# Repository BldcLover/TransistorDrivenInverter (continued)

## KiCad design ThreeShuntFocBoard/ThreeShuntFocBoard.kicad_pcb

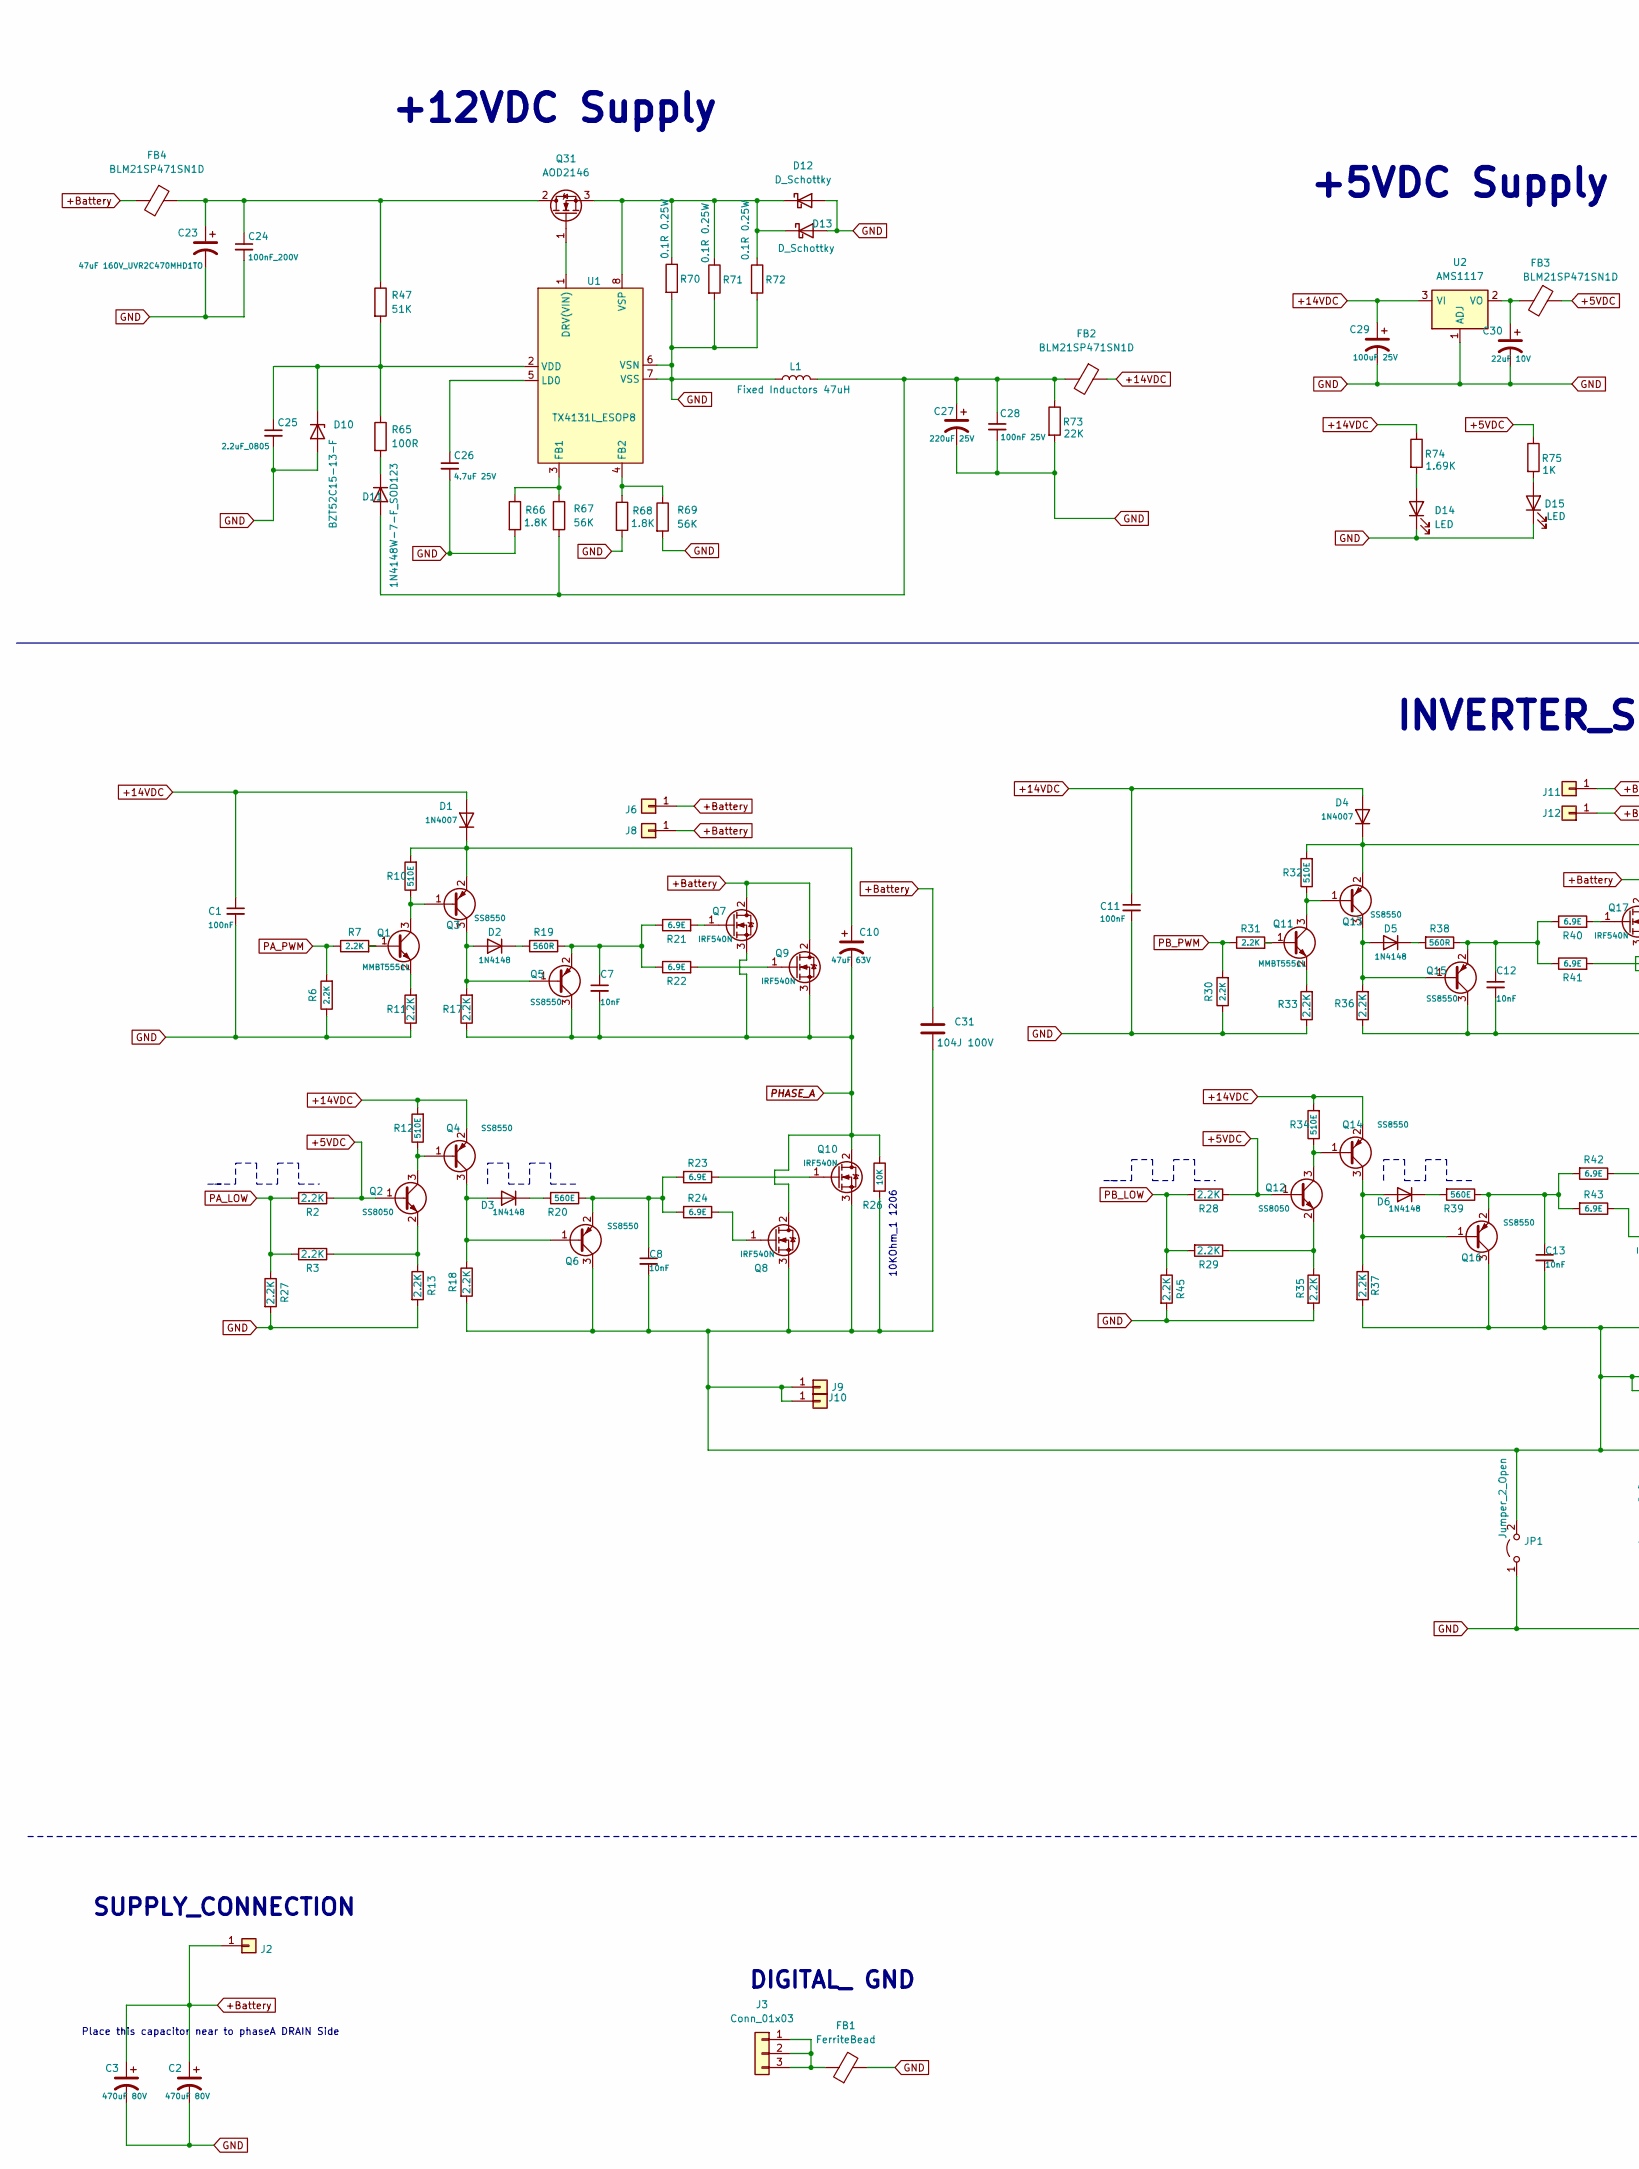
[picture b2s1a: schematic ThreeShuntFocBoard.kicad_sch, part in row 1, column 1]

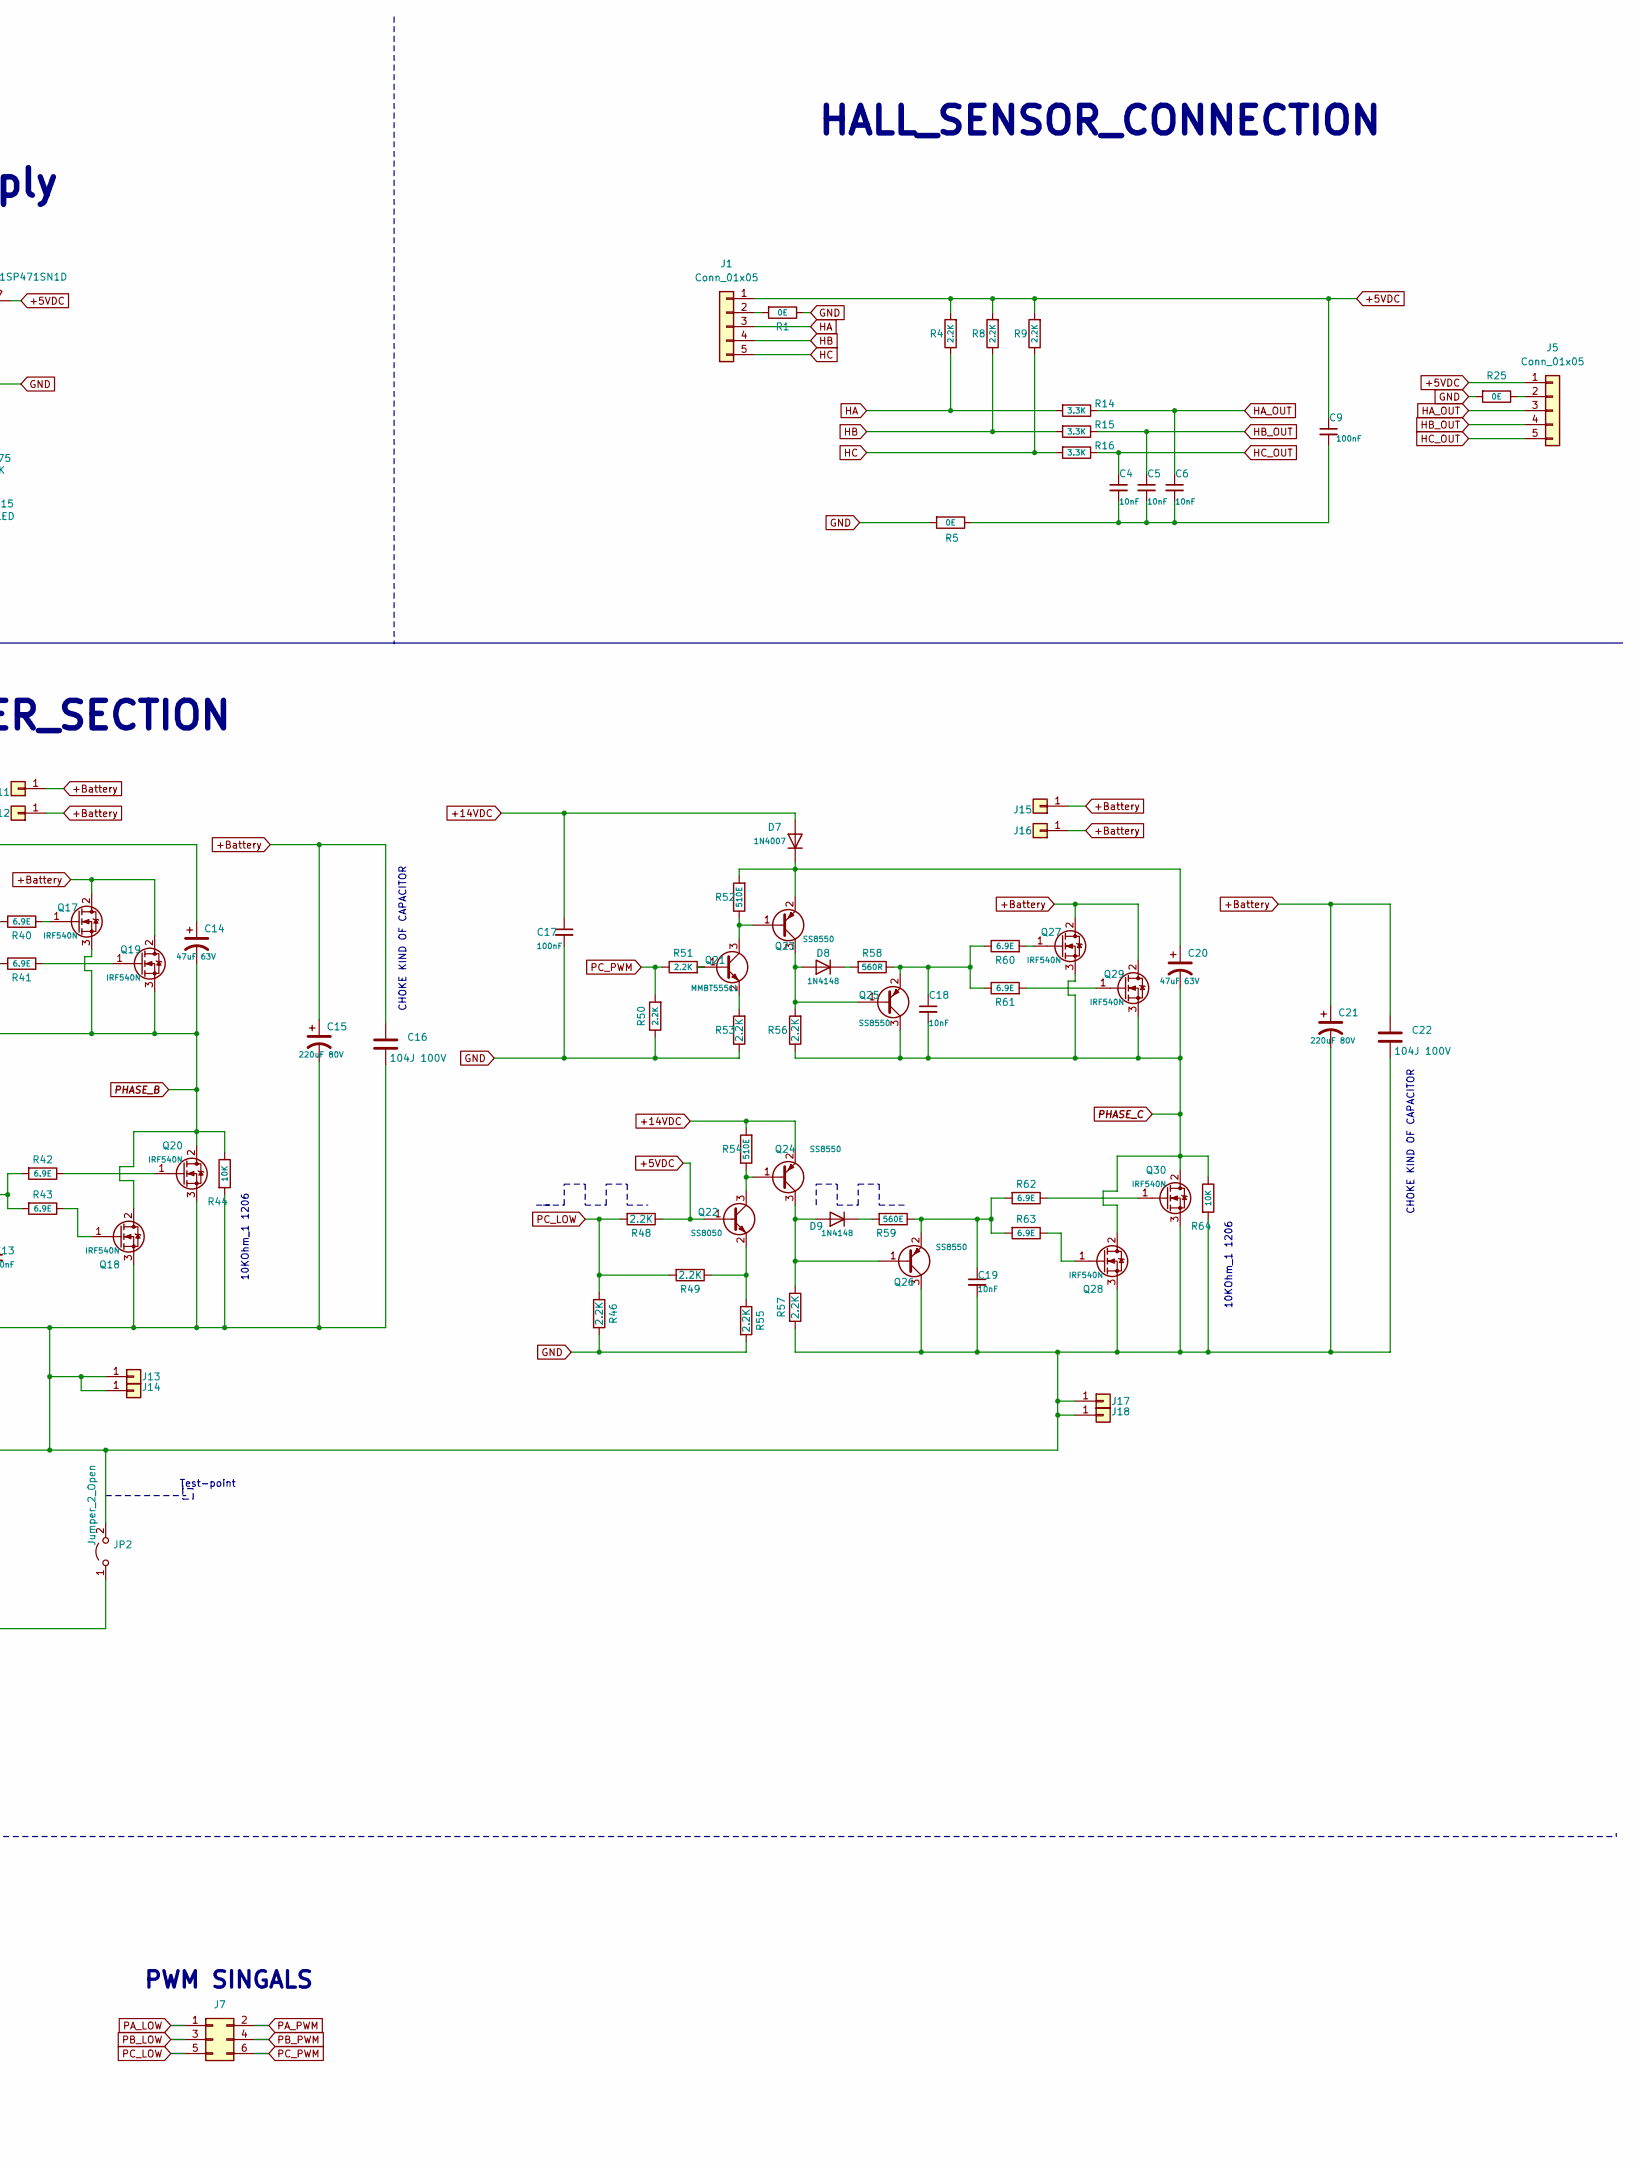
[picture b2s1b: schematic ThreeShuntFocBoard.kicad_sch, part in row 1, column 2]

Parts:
C1, C9, C11, C17: 100nF; C_0603
C2, C3: 470uF 80V; 220uF_80VDC
C4, C5, C6, C7, C8, C12, C13, C18, C19: 10nF; C_0603
C10, C14, C20: 47uF 63V; 220uF63V
C15, C21: 220uF 80V; 220uF_80VDC
C16, C22, C31: 104J 100V; 104J_100V
C23: 47uF 160V_UVR2C470MHD1TO; 47uF_25V
C24: 100nF_200V; 0.1uF200V
C25: 2.2uF_0805; 1206_C
C26: 4.7uF 25V; C_0603
C27: 220uF 25V
C28: 100nF 25V; C_0603
C29: 100uF 25V; 100uF 25V_2917
C30: 22uF 10V
D1, D4, D7: 1N4007; ZenerDiode_S1M
D2, D3, D5, D6, D8, D9: 1N4148; SOD_123_v1
D10: BZT52C15-13-F
D11: 1N4148W-7-F_SOD123; SOD_123_v1
D12, D13: D_Schottky; SS24-HF
D14, D15: LED; LED_0603
FB1: FerriteBead; BLM21SP471SN1D
FB2, FB3, FB4: BLM21SP471SN1D
J1, J5: Conn_01x05; Socket_Strip_Straight_1x05_Pitch2.54mm
J2, J6, J8, J9, J10, J11, J12, J13, J14, J15, J16, J17, J18: Conn_01x01; Powe_pad
J3: Conn_01x03; Socket_Strip_Straight_1x03_Pitch2.54mm
J7: Conn_02x03_Odd_Even; Socket_Strip_Straight_oddeven_2x06_Pitch2.54mm
JP1, JP2: Jumper_2_Open; 104J_100V
L1: Fixed Inductors 47uH; 47uH_Inductor
Q1, Q11, Q21: MMBT5551L; SOT-23_v1
Q2, Q12, Q22: SS8050; SOT-23_v1
Q3, Q4, Q5, Q6, Q13, Q14, Q15, Q16, Q23, Q24, Q25, Q26: SS8550; SOT-23_v1
Q7, Q8, Q9, Q10, Q17, Q18, Q19, Q20, Q27, Q28, Q29, Q30: IRF540N; TO-220-3_Vertical
Q31: AOD2146; AOD4126
R1, R5, R25: 0E; R_0603
R2, R3, R4, R6, R7, R8, R9, R11, R13, R17, R18, R27, R28, R29, R30, R31, R33, R35, R36, R37, R45, R46, R48, R49, R50, R51, R53, R55, R56, R57: 2.2K; R_0603
R10, R12, R32, R34, R52, R54: 510E; R_0603
R14, R15, R16: 3.3K; R_0603
R19, R38, R58: 560R; R_0603
R20, R39, R59: 560E; R_0603
R21, R22, R23, R24, R40, R41, R42, R43, R60, R61, R62, R63: 6.9E; R_0603
R26, R44, R64: 10K; 1206_R
R47: 51K; 1206_R
R65: 100R; R_0603
R66, R68: 1.8K; R_0603
R67, R69: 56K; R_0603
R70, R71, R72: 0.1R 0.25W
R73: 22K; R_0603
R74: 1.69K; R_0603
R75: 1K; R_0603
U1: TX4131L_ESOP8
U2: AMS1117; AMS1117 SOT-223

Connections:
+5VDC: C9.1, FB3.1, J1.1, J5.1, Q2.1 (B), Q12.1 (B), Q22.1 (B), R2.1, R4.2, R8.2, R9.2, R28.1, R48.1, R75.1
+14VDC: C1.1, C11.1, C17.1, C29.1, D1.2 (A), D4.2 (A), D7.2 (A), FB2.1, Q4.2 (E), Q14.2 (E), Q24.2 (E), R12.2, R34.2, R54.2, R74.1, U2.3 (VI)
+Battery: C2.1, C3.1, C15.1, C16.1, C21.1, C22.1, C31.1, FB4.2, J2.1, J6.1, J8.1, J11.1, J12.1, J15.1, J16.1, Q7.2 (D), Q9.2 (D), Q17.2 (D), Q19.2 (D), Q27.2 (D), Q29.2 (D)
GND: C1.2, C2.2, C3.2, C11.2, C17.2, C23.2, C24.2, C25.2, C26.2, C27.2, C28.2, C29.2, C30.2, D10.2 (A), D12.2 (A), D13.2 (A), D14.1 (K), D15.1 (K), FB1.2, JP1.1 (A), JP2.1 (A), L1.1, R1.1, R5.2, R6.1, R11.1, R13.2, R25.2, R27.2, R30.1, R33.1, R35.2, R45.2, R46.2, R50.1, R53.1, R55.2, R66.2, R68.2, R69.2, R70.2, R71.2, R72.2, R73.2, U1.6 (VSN), U1.7 (VSS), U2.1 (ADJ)
HA: J1.3, R4.1, R14.2
HA_OUT: C6.1, J5.3, R14.1
HB: J1.4, R8.1, R15.2
HB_OUT: C5.1, J5.4, R15.1
HC: J1.5, R9.1, R16.2
HC_OUT: C4.1, J5.5, R16.1
unnamed: C4.2, C5.2, C6.2, C9.2, R5.1
unnamed: C7.1, Q5.2 (E), R19.1, R21.1, R22.1
unnamed: C8.1, Q6.2 (E), R20.1, R23.2, R24.2
unnamed: C10.1, D1.1 (K), Q3.2 (E), R10.2
unnamed: C12.1, Q15.2 (E), R38.1, R40.1, R41.1
unnamed: C13.1, Q16.2 (E), R39.1, R42.2, R43.2
unnamed: C8.2, C13.2, C15.2, C16.2, C19.2, C21.2, C22.2, C31.2, J9.1, J10.1, J13.1, J14.1, J17.1, J18.1, JP1.2 (B), JP2.2 (B), Q6.3 (C), Q8.3 (S), Q10.3 (S), Q16.3 (C), Q18.3 (S), Q20.3 (S), Q26.3 (C), Q28.3 (S), Q30.3 (S), R18.2, R26.2, R37.2, R44.2, R57.2, R64.2
unnamed: C14.1, D4.1 (K), Q13.2 (E), R32.2
unnamed: C18.1, Q25.2 (E), R58.1, R60.1, R61.1
unnamed: C19.1, Q26.2 (E), R59.1, R62.2, R63.2
unnamed: C20.1, D7.1 (K), Q23.2 (E), R52.2
unnamed: C23.1, C24.1, FB4.1, Q31.2 (D), R47.1
unnamed: C25.1, D10.1 (K), R47.2, R65.1, U1.2 (VDD)
unnamed: C26.1, U1.5 (LD0)
unnamed: C27.1, C28.1, D11.2 (A), FB2.2, L1.2, R67.2, R73.1
unnamed: C30.1, FB3.2, U2.2 (VO)
unnamed: D2.1 (K), R19.2
unnamed: D2.2 (A), Q3.3 (C), Q5.1 (B), R17.2
unnamed: D3.1 (K), R20.2
unnamed: D3.2 (A), Q4.3 (C), Q6.1 (B), R18.1
unnamed: D5.1 (K), R38.2
unnamed: D5.2 (A), Q13.3 (C), Q15.1 (B), R36.2
unnamed: D6.1 (K), R39.2
unnamed: D6.2 (A), Q14.3 (C), Q16.1 (B), R37.1
unnamed: D8.1 (K), R58.2
unnamed: D8.2 (A), Q23.3 (C), Q25.1 (B), R56.2
unnamed: D9.1 (K), R59.2
unnamed: D9.2 (A), Q24.3 (C), Q26.1 (B), R57.1
unnamed: D11.1 (K), R65.2
unnamed: D12.1 (K), D13.1 (K), Q31.3 (S), R70.1, R71.1, R72.1, U1.8 (VSP)
unnamed: D14.2 (A), R74.2
unnamed: D15.2 (A), R75.2
unnamed: FB1.1, J3.1, J3.2, J3.3
unnamed: J1.2, R1.2
unnamed: J5.2, R25.1
unnamed: Q1.1 (B), R7.2
unnamed: Q1.2 (E), R11.2
unnamed: Q1.3 (C), Q3.1 (B), R10.1
unnamed: Q2.2 (E), R3.1, R13.1
unnamed: Q2.3 (C), Q4.1 (B), R12.1
unnamed: Q7.1 (G), R21.2
unnamed: Q8.1 (G), R24.1
unnamed: Q9.1 (G), R22.2
unnamed: Q10.1 (G), R23.1
unnamed: Q11.1 (B), R31.2
unnamed: Q11.2 (E), R33.2
unnamed: Q11.3 (C), Q13.1 (B), R32.1
unnamed: Q12.2 (E), R29.1, R35.1
unnamed: Q12.3 (C), Q14.1 (B), R34.1
unnamed: Q17.1 (G), R40.2
unnamed: Q18.1 (G), R43.1
unnamed: Q19.1 (G), R41.2
unnamed: Q20.1 (G), R42.1
unnamed: Q21.1 (B), R51.2
unnamed: Q21.2 (E), R53.2
unnamed: Q21.3 (C), Q23.1 (B), R52.1
unnamed: Q22.2 (E), R49.1, R55.1
unnamed: Q22.3 (C), Q24.1 (B), R54.1
unnamed: Q27.1 (G), R60.2
unnamed: Q28.1 (G), R63.1
unnamed: Q29.1 (G), R61.2
unnamed: Q30.1 (G), R62.1
unnamed: Q31.1 (G), U1.1 (DRV(VIN))
unnamed: R66.1, R67.1, U1.3 (FB1)
unnamed: R68.1, R69.1, U1.4 (FB2)
PA_LOW: J7.1, R2.2, R3.2, R27.1
PA_PWM: J7.2, R6.2, R7.1
PB_LOW: J7.3, R28.2, R29.2, R45.1
PB_PWM: J7.4, R30.2, R31.1
PC_LOW: J7.5, R46.1, R48.2, R49.2
PC_PWM: J7.6, R50.2, R51.1
PHASE_A: C7.2, C10.2, Q5.3 (C), Q7.3 (S), Q8.2 (D), Q9.3 (S), Q10.2 (D), R17.1, R26.1
PHASE_B: C12.2, C14.2, Q15.3 (C), Q17.3 (S), Q18.2 (D), Q19.3 (S), Q20.2 (D), R36.1, R44.1
PHASE_C: C18.2, C20.2, Q25.3 (C), Q27.3 (S), Q28.2 (D), Q29.3 (S), Q30.2 (D), R56.1, R64.1

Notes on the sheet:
INVERTER_SECTION
DIGITAL_ GND
10KOhm_1 1206
HALL_SENSOR_CONNECTION
SUPPLY_CONNECTION
CHOKE KIND OF CAPACITOR
+5VDC Supply
+12VDC Supply
Test-point
PWM SINGALS
Place this capacitor near to phaseA DRAIN Side

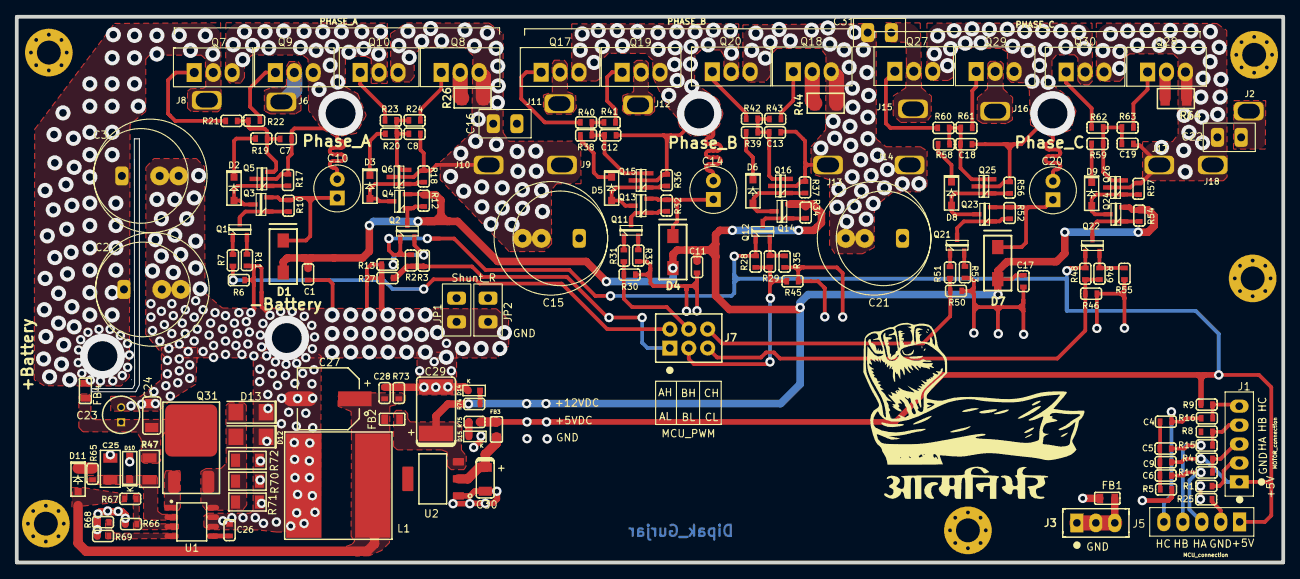
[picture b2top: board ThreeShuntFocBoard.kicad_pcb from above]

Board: 2 copper layers, 169.9 x 73.2 mm, 178 parts (0 on the bottom side), 84 nets.

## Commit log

2025-03-23 Commit: 1 All section is working except power supply section.
2025-03-23 Only PhaseA inverter section is implemented : need to review
2025-03-25 commit 2: Updated Power Supply, Safety Fuse, Phase Design, and Hall Sensor Circuit
    for more details read ChangesDetial.txt in same folder.
2025-03-27 Commit 3: Assigned STM32G431C6Tx (LQFP-48) pins as per the shared Excel, peripheral connections WIP, Phase C current sensing removed due to ADC group limitations
    read attach excel files and changesDetails.txt file for more detail
2025-03-28 Commit 4: updated the schematic
    Added crystal load capacitors, test points, SWO for debugging, PB8 as boot/CAN_RX, Pi filter on VDDA, and noted peripherals.
2025-03-30 Commit 5: Improved power integrity and ADC accuracy.
    for more details read changesDetail.txt file
2025-06-03 UnderDeveloment: Design FOC based board using STM32F103
    Note:
    - Currrently board is 2 layer stack up and planning to make it 4 layer for better performance
    - Not tested
2025-06-07 Design 4 layer Board with separate supply and ground plane
    Note:
    Below points WIP...
    -Need to check all the plane.
    -Place ground via if needed near to shunt and return path of the supply.
    -Validate the layout.
